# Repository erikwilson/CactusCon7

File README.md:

# CactusCoin

## Hack All The Things

This year's badge is based around a TTGO LoRa OLED ESP32 and contains six capacitive 'buttons' driven from four sensor inputs (classic [n choose floor(n/2)](http://www.wolframalpha.com/input/?i=n+choose+floor(n%2F2)) problem). The ESP32 sports 4MB of programmable flash, WiFi, Bluetooth, and a dual core 240MHz processor, mounted on a board with a 433MHz long range radio, display, and lipo charger. It requires a single 18650 lithium ion rechargable battery. Optional circuitry supports a motor driver which operates on the same lines as the OLED by disabling screen controls when using the motor controller.  Add in some d-pad action, motors, wheels, and a jöystick. It has an access point, captive portal, websockets, and hidden secrets. The firmware was written using Arduino. It’s completely hackable. Wear it, play with it, use it, modify it, break it, learn from it.

## Volunteering

Every year countless hackers toil for endless hours to bring you this most exquisite and bespoke artisanal CactusCon experience. Please email badge@cactuscon.com if you wish to sacrifice yourself and contribute to the great process. Help build the global hacker community!

## ̶B̶u̶g̶s̶ ̶ Features and Pull Requests

Feel free to submit issues, or even better submit a pull request with extra functionality!

The coin provides a swiss army knife of utility, what can you make with it?

## Parts

#### basic

* 1 [TTGO LoRa OLED ESP32](https://www.aliexpress.com/item/2pcs-sets-TTGO-LORA-SX1278-ESP32-0-96-OLED-16-Mt-bytes-128-Mt-bit-433Mhz/32832523252.html)
* 2 x [18 pos female header](https://www.digikey.com/product-detail/en/PPTC181LFBN-RC/S7016-ND/810156/?itemSeq=272349209)
* 1 [battery holder](https://www.digikey.com/product-detail/en/BH-18650-PC/BH-18650-PC-ND/3029216/?itemSeq=272342283)
* 1 [switch](https://www.digikey.com/product-detail/en/MHSS1105/679-1849-ND/1949465/?itemSeq=272294708)

#### bot upgrade

* 1 [Motor driver](https://www.sparkfun.com/products/14450)
* 2 x [8 pos female header](https://www.digikey.com/product-detail/en/sullins-connector-solutions/PPTC081LFBN-RC/S7006-ND/810147)
* 1 [set Wheels](https://www.sparkfun.com/products/13259)
* 1 [set Motors](https://www.sparkfun.com/products/13302)
* 2 x [2 pos female header](https://www.digikey.com/product-detail/en/sullins-connector-solutions/PPPC021LFBN-RC/S7035-ND/810174)
* 9v [battery connector](https://www.digikey.com/products/en?keywords=36-232-ND) (optional, can use 18650 power instead)
* 1.5" x 3 [Velcro Tape](https://www.amazon.com/VELCRO-Brand-Sticky-Fasteners-Perfect/dp/B00006IC2L)
* 2 x [Zip Tie](https://www.amazon.com/dp/B01018DC96/)
* 1 [Joystick](https://www.sparkfun.com/products/9032P) (for seperate badge)

## Additional Arduino Libraries

* https://github.com/intrbiz/arduino-crypto
* https://github.com/sandeepmistry/arduino-LoRa
* https://github.com/ThingPulse/esp8266-oled-ssd1306
* https://github.com/bblanchon/ArduinoJson
* https://github.com/me-no-dev/AsyncTCP
* https://github.com/me-no-dev/ESPAsyncWebServer
* https://github.com/me-no-dev/EspExceptionDecoder
* https://github.com/me-no-dev/arduino-esp32fs-plugin

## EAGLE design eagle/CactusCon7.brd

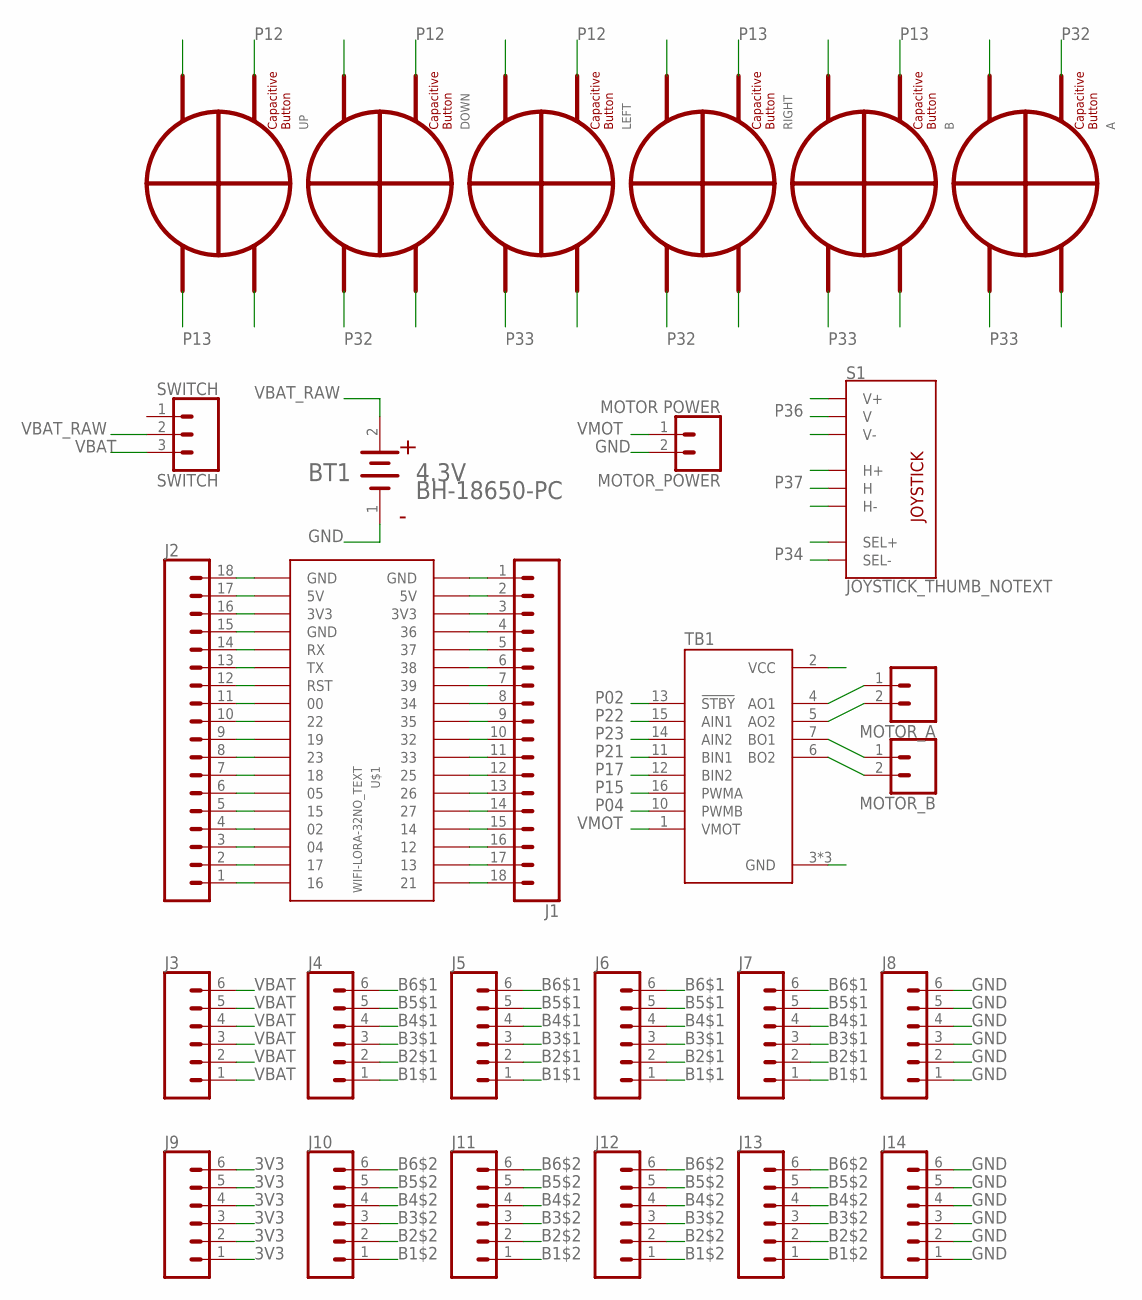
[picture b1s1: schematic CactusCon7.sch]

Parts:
A: BUTTON_ACTIVE_QUADNO-LOGO; BUTTON_ACTIVE_QUAD_10MM_NO_LOGO
B: BUTTON_ACTIVE_QUADNO-LOGO; BUTTON_ACTIVE_QUAD_10MM_NO_LOGO
BT1: MPD_BH-18650-PCMPD_BH-18650-PC_0_0; MPD_BH-18650-PC_0
DOWN: BUTTON_ACTIVE_QUADNO-LOGO; BUTTON_ACTIVE_QUAD_10MM_NO_LOGO
J1, J2: CONN_18; 1X18
J3, J4, J5, J6, J7, J8, J9, J10, J11, J12, J13, J14: CONN_06NO_SILK_FEMALE_PTH; 1X06_NO_SILK
LEFT: BUTTON_ACTIVE_QUADNO-LOGO; BUTTON_ACTIVE_QUAD_10MM_NO_LOGO
MOTOR_A: CONN_02; 1X02
MOTOR_B: CONN_02; 1X02
MOTOR_POWER: MOTOR POWER; 1X02
RIGHT: BUTTON_ACTIVE_QUADNO-LOGO; BUTTON_ACTIVE_QUAD_10MM_NO_LOGO
S1: JOYSTICK_THUMB_NOTEXT; JOYSTICK
SWITCH: SWITCH; 1X03
TB1: POLOLU-713ROB-14451; SHIELD_POLOLU-713
U$1: WIFI-LORA-32NO_TEXT; 2.54MM_2X18_NO_TEXT
UP: BUTTON_ACTIVE_QUADNO-LOGO; BUTTON_ACTIVE_QUAD_10MM_NO_LOGO

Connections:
3V3: J1.3, J2.16, J9.1, J9.2, J9.3, J9.4, J9.5, J9.6, S1.B1A (SEL+), S1.H1 (H+), S1.V1 (V+), TB1.2 (VCC), U$1.P$3 (3V3), U$1.P$34 (3V3)
5V: J1.2, J2.17, U$1.P$2 (5V), U$1.P$35 (5V)
AO1: MOTOR_A.1, TB1.4 (AO1)
AO2: MOTOR_A.2, TB1.5 (AO2)
B1$1: J4.1, J5.1, J6.1, J7.1
B1$2: J10.1, J11.1, J12.1, J13.1
B2$1: J4.2, J5.2, J6.2, J7.2
B2$2: J10.2, J11.2, J12.2, J13.2
B3$1: J4.3, J5.3, J6.3, J7.3
B3$2: J10.3, J11.3, J12.3, J13.3
B4$1: J4.4, J5.4, J6.4, J7.4
B4$2: J10.4, J11.4, J12.4, J13.4
B5$1: J4.5, J5.5, J6.5, J7.5
B5$2: J10.5, J11.5, J12.5, J13.5
B6$1: J4.6, J5.6, J6.6, J7.6
B6$2: J10.6, J11.6, J12.6, J13.6
BO1: MOTOR_B.1, TB1.7 (BO1)
BO2: MOTOR_B.2, TB1.6 (BO2)
GND: A.Q2, A.Q4, B.Q2, B.Q4, BT1.1 (CATHODE), DOWN.Q2, DOWN.Q4, J1.1, J2.15, J2.18, J8.1, J8.2, J8.3, J8.4, J8.5, J8.6, J14.1, J14.2, J14.3, J14.4, J14.5, J14.6, LEFT.Q2, LEFT.Q4, MOTOR_POWER.2, RIGHT.Q2, RIGHT.Q4, S1.H3 (H-), S1.V3 (V-), TB1.3 (GND), TB1.8 (GND), TB1.9 (GND), U$1.P$1 (GND), U$1.P$4 (GND), U$1.P$36 (GND), UP.Q2, UP.Q4
P00: J2.11, U$1.P$8 (00)
P02: J2.4, TB1.13 (!STBY), U$1.P$15 (02)
P04: J2.3, TB1.10 (PWMB), U$1.P$16 (04)
P05: J2.6, U$1.P$13 (05)
P12: DOWN.Q3, J1.16, LEFT.Q3, U$1.P$21 (12), UP.Q3
P13: B.Q3, J1.17, RIGHT.Q3, U$1.P$20 (13), UP.Q1
P14: J1.15, U$1.P$22 (14)
P15: J2.5, TB1.16 (PWMA), U$1.P$14 (15)
P16: J2.1, U$1.P$18 (16)
P17: J2.2, TB1.12 (BIN2), U$1.P$17 (17)
P18: J2.7, U$1.P$12 (18)
P19: J2.9, U$1.P$10 (19)
P21: J1.18, TB1.11 (BIN1), U$1.P$19 (21)
P22: J2.10, TB1.15 (AIN1), U$1.P$9 (22)
P23: J2.8, TB1.14 (AIN2), U$1.P$11 (23)
P25: J1.12, U$1.P$25 (25)
P26: J1.13, U$1.P$24 (26)
P27: J1.14, U$1.P$23 (27)
P32: A.Q3, DOWN.Q1, J1.10, RIGHT.Q1, U$1.P$27 (32)
P33: A.Q1, B.Q1, J1.11, LEFT.Q1, U$1.P$26 (33)
P34: J1.8, S1.B2A (SEL-), U$1.P$29 (34)
P35: J1.9, U$1.P$28 (35)
P36: J1.4, S1.V2 (V), U$1.P$33 (36)
P37: J1.5, S1.H2 (H), U$1.P$32 (37)
P38: J1.6, U$1.P$31 (38)
P39: J1.7, U$1.P$30 (39)
RST: J2.12, U$1.P$7 (RST)
RX: J2.14, U$1.P$5 (RX)
TX: J2.13, U$1.P$6 (TX)
VBAT: J3.1, J3.2, J3.3, J3.4, J3.5, J3.6, SWITCH.3
VBAT_RAW: BT1.2 (ANODE), SWITCH.2
VMOT: MOTOR_POWER.1, TB1.1 (VMOT)

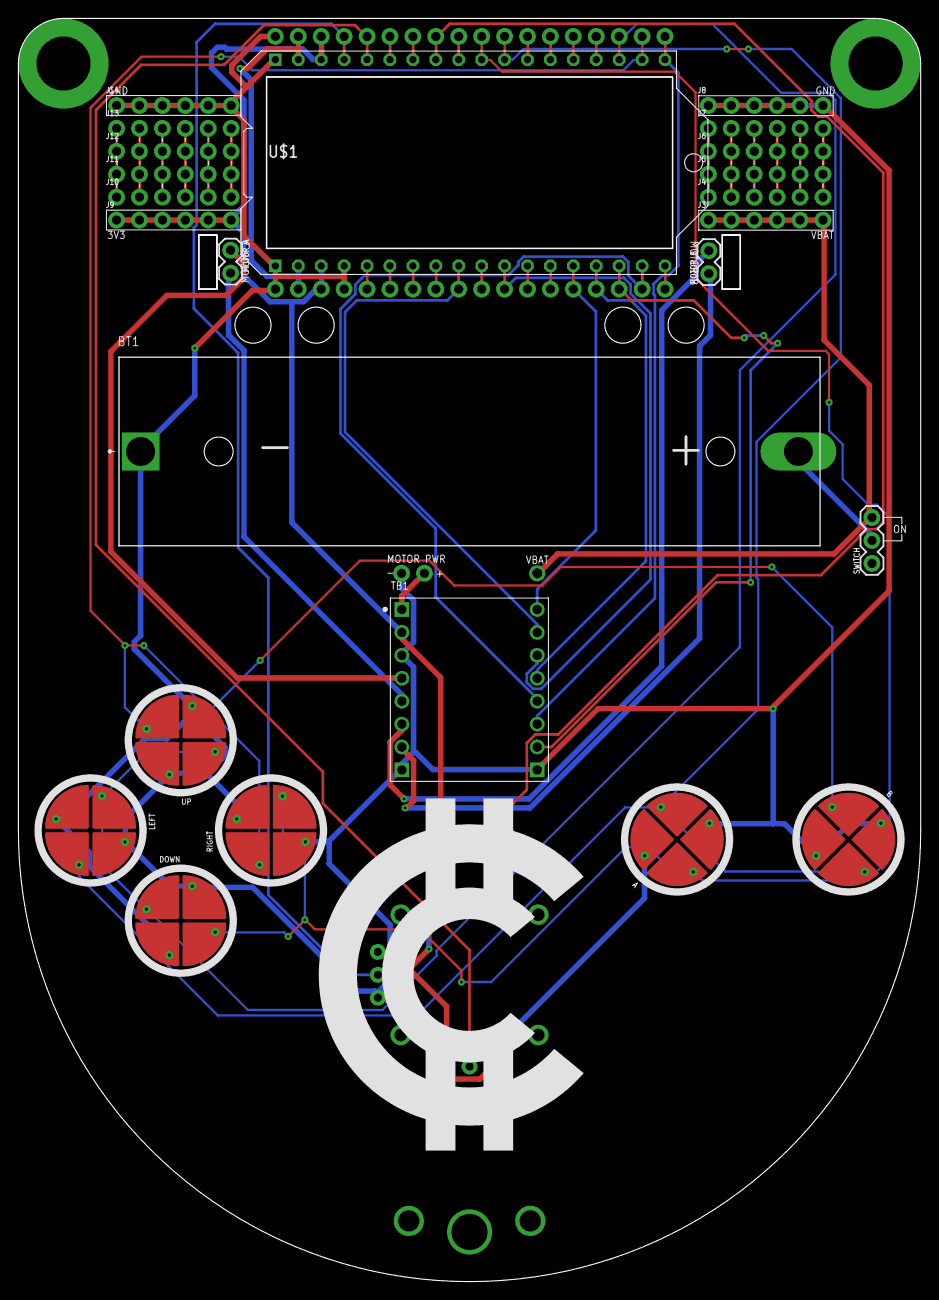
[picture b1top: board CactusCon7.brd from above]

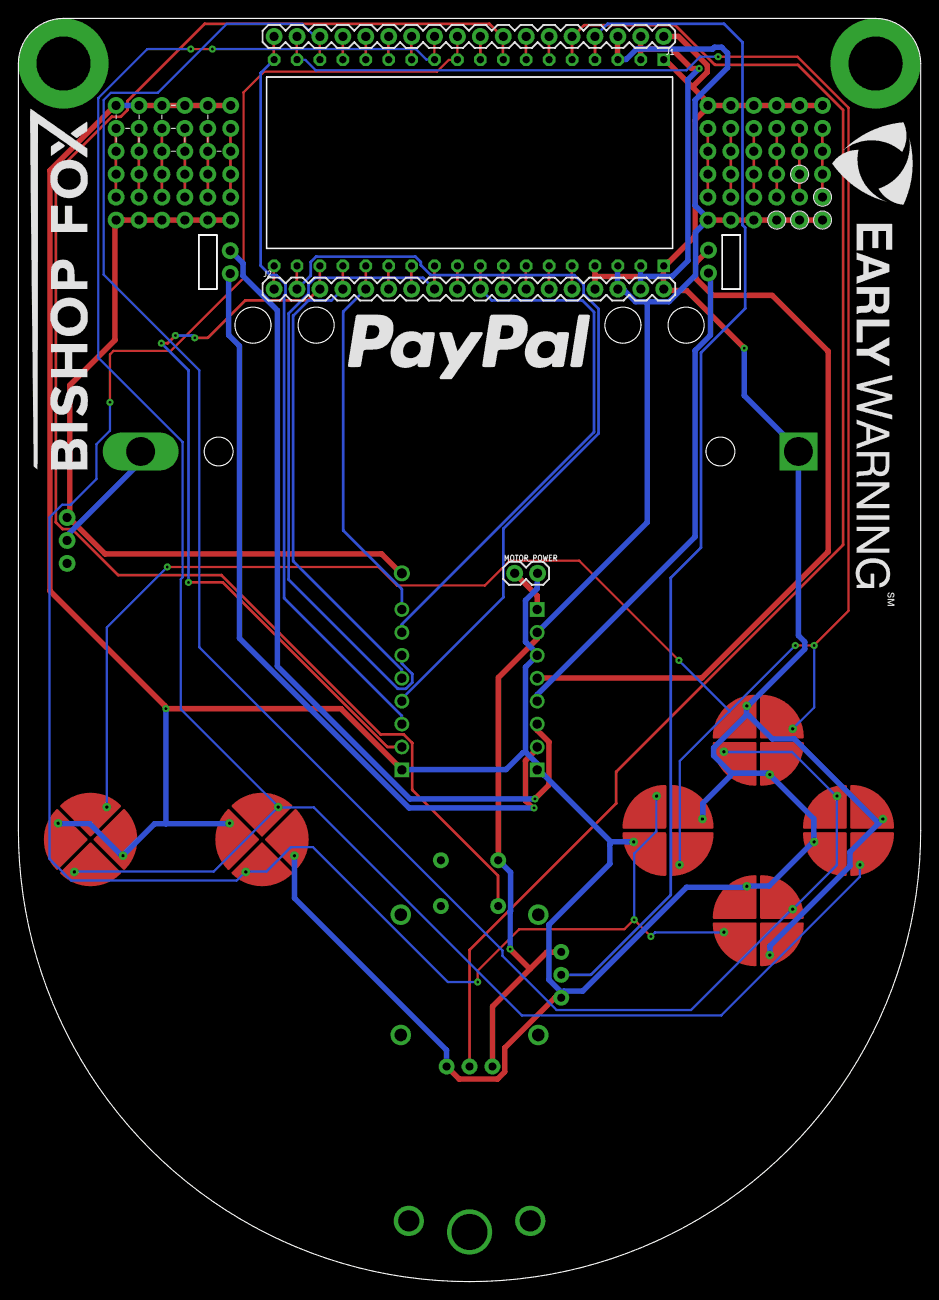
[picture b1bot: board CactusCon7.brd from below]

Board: 2 copper layers, 99.9 x 139.9 mm, 28 parts (3 on the bottom side), 51 nets.

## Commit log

2018-03-21 initial
2018-03-21 more header
2018-08-19 its messy, just getting warmed up
2018-08-22 added additional badge key and vim swp files to be ignored by git
2018-08-22 renamed badge keypair
2018-08-22 fixed for python3 and added exception wrapping for invalid signatures on verify
2018-08-22 moved to python3, added handling of signature check failures, added badge data validation checks, and set test environment to load two badge keys
2018-08-22 a bit of refactoring to better support multiple keys during testing, updated test to allow clients to update existing badge data, added test to ensure badges signatures are being validated, and also 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
2018-08-23 started on coin submission test and endpoint
2018-08-25 submit coin mostly working, still more changes... big refactor coming up next
2018-08-25 massive refactor... now its starting to look less messy and like a real python package :)
2018-08-25 filled in a few things from a template readme
2018-08-25 added get support for the coin endpoint to return a list of connected badges
2018-08-25 added some mocking requirements
2018-08-25 made invalid/valid coin fixtures
2018-08-25 added tests submitting a invalid coin and getting coins
2018-08-26 added some docstrings
2018-08-26 minor name cleanup
2018-08-26 enabled coverage checking on test
2018-08-26 minor comments
2018-08-29 lora oled examples
2018-08-29 renamed leaderboard
2018-08-29 gave 1 point to folks for registering
2018-08-29 added score when coin is reported and scoreboard endpoint
2018-08-29 added scoreboard test
2018-08-31 updated with some basic instructions for running in dev mode
2018-08-31 change to use cfg file as set by env variable
2018-08-31 added cfg file env variable to example
2018-08-31 fixed bug where name changes were causing points to accumulate
2018-08-31 moved mock redis and stuff to be monkeypatched in instead
2018-08-31 added cfg file and keys to handle it better
2018-08-31 touch
2018-09-01 started CDP doc
2018-09-01 commiting without spellchecking... i live dangerously
2018-09-06 binary protocol is still a work in progress, getting close though, checking in under a feature branch for now
2018-09-10 fixed and working now, little messy, but it'll do
2018-09-10 moved protocol spec to higher level dir
2018-09-15 just starting to get warmed up.. badges can send and receive now
2018-09-16 more mucking about, getting ready to write library to handle binary protocol
2018-09-16 set this back to just use base64 since we'll be transmitting coins via wifi... api should run now again
2018-09-20 first pass of packing/unpacking with just type casting... appears to be working well, but nested structs are having an issue.
2018-09-21 needs some refactoring now, but just about to the point of where 3 way exchange is functional and can move on to wifi submit
2018-09-23 got spiffs working
2018-09-23 mbedtls
2018-09-24 a bit slower tonight than hoped, rsa is integrated i think, but not tested. will give it a go tomorrow and then come back to the buffered coin stuff
2018-09-25 somehow... this is working now... pretty sure void casting structs across the wire was a mistake now... oh well.
2018-09-26 looks like local coin buffering is working now, onto rsa and finishing submittal
2018-09-26 argh, just when i thought i had this fixed i discovered more bugs... most squashed, but need to decide what happens when a duplicate CSR shows up
2018-09-26 sample touch code
2018-09-26 fixed duplicate csr issue, few other fs issues, and now close to having it able to submit... some stack overflow issue though when signing message for api, will look at it when i get back
2018-09-27 mother of all updates.. fixed lots of bugs, adjusted api to match badge json, basic use case is now fully functional!! still needs some tuning and there is one odd bug where badges still transmit csr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
2018-09-27 updated touch
2018-09-28 added paginated list for coin lists
2018-09-28 just about there, pagination working, signatures almost verifying
2018-09-28 added spiffs generator
2018-09-28 added signed http status codes for responses to badges
2018-09-28 added verification of api responses... looking pretty good now
2018-09-28 fixed some bugs, seems there are a couple more
2018-09-28 touched
2018-09-28 no wrap
2018-09-29 initail "ui" import
2018-09-29 fixed bugs in the backend
2018-09-29 lots o bug fixes, should be solid now.. i think.. maybe
2018-09-29 added support for sponsorship whoring :) and fixed ids > 1 byte
2018-09-29 maybe this is the bug?
2018-09-29 ui works... aint pretty, but it works
2018-09-29 no registration coin for you
2018-09-29 put this back to getting real names
2018-09-29 docker
2018-09-29 morning
2018-09-29 creds
2018-09-29 all rssi
2018-09-29 esptool
2018-09-29 make
2018-09-29 woops
2018-10-03 cleanup
2018-10-03 readme
2018-10-05 images
2018-10-05 words
2018-10-05 mv readme
2018-10-05 duck
2018-10-05 mv www
2018-10-05 bot data
2019-01-03 add build

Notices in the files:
parts and their libraries:
PatternAgents-TouchWidgets: License : http://creativecommons.org/licenses/by-sa/4.0/ (Creative Commons 4.0)
PatternAgents-TouchWidgets: License : http://creativecommons.org/licenses/by-sa/3.1/ (Creative Commons 3.1)
